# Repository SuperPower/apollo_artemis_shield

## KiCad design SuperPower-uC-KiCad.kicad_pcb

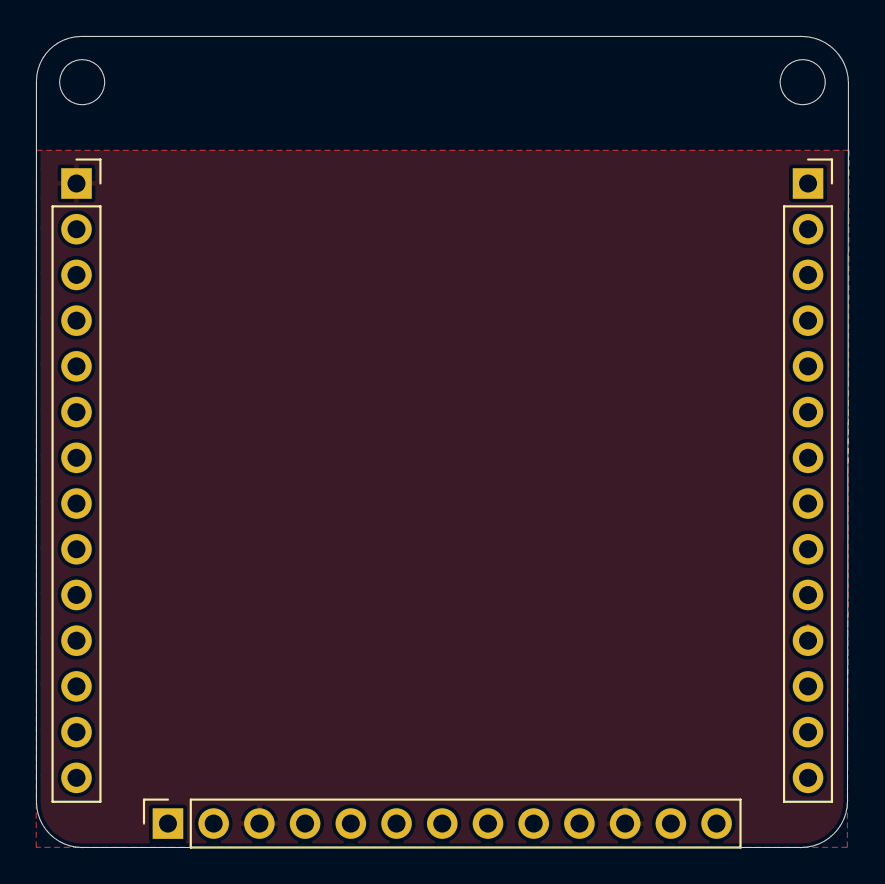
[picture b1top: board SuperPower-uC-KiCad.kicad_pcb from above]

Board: 4 copper layers, 45.1 x 45.1 mm, 5 parts (0 on the bottom side), 6 nets.

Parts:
H5, H6: MountingHole_Pad; MountingHole_2.5mm
J5, J6: Conn_01x14_Female; PinSocket_1x14_P2.54mm_Vertical
J9: MCU board; PinSocket_1x13_P2.54mm_Vertical

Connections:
/EN_3v3: J6.13, J9.9
/EN_5v: J6.14, J9.7
/SCL_2: J5.3, J9.1
/SDA_2: J5.6, J9.2
/~SMBALERT: J6.7, J9.13
GND: H5.1, H6.1, J6.1, J9.3, J9.11

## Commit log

2021-01-30 added base files
2021-02-06 Add gitignore file
2021-02-06 Add copper area to top layer as well
